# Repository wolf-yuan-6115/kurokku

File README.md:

# Kurokku

Kurokku is an ESP32 based Wi-Fi smart clock. Featuring E-ink display, it can pull weather data, calendar and display realtime clock. It is designed to be a simple and elegant clock that can be placed on a desk. There's also a SHT40 temperature and humidity sensor to provide more information.

Case was not designed and it's intended to just directly use screw as stand.

> [!NOTE]
> Please don't expect me to find a 3D model for e-ink display and include it.

> Note that display is not here yet because it's going to order seperately.

## Schematic

## Routing

## BOM

| Name | Qty | Total (USD) | Distributor |
| --- | --- | --- | --- |
| [Waveshare e-ink display](https://detail.tmall.com/item.htm?from=cart&id=763853854896&mi_id=0000evqKCP1iKHChQN8zlU8k7eiaN9Pw3tzSlfQsYnoQPNw&skuId=5256424296363&upStreamPrice=13068) | 1 | 19.50 | Taobao |
| [Seeed Xiao ESP32-S3](https://item.taobao.com/item.htm?from=cart&id=717378181472&mi_id=0000sOOkvg8oup2ws_yxejnEZ-Q6HdgFkvkQyJaaRKFnI_o&upStreamPrice=5500) | 1 | 8.20 | Taobao |
| PCB & PCBA | 1 | 28.96 | JLCPCB |
| Shipping | 1 | 0.5 | Taobao |
| Total | - | 57.16 | - |

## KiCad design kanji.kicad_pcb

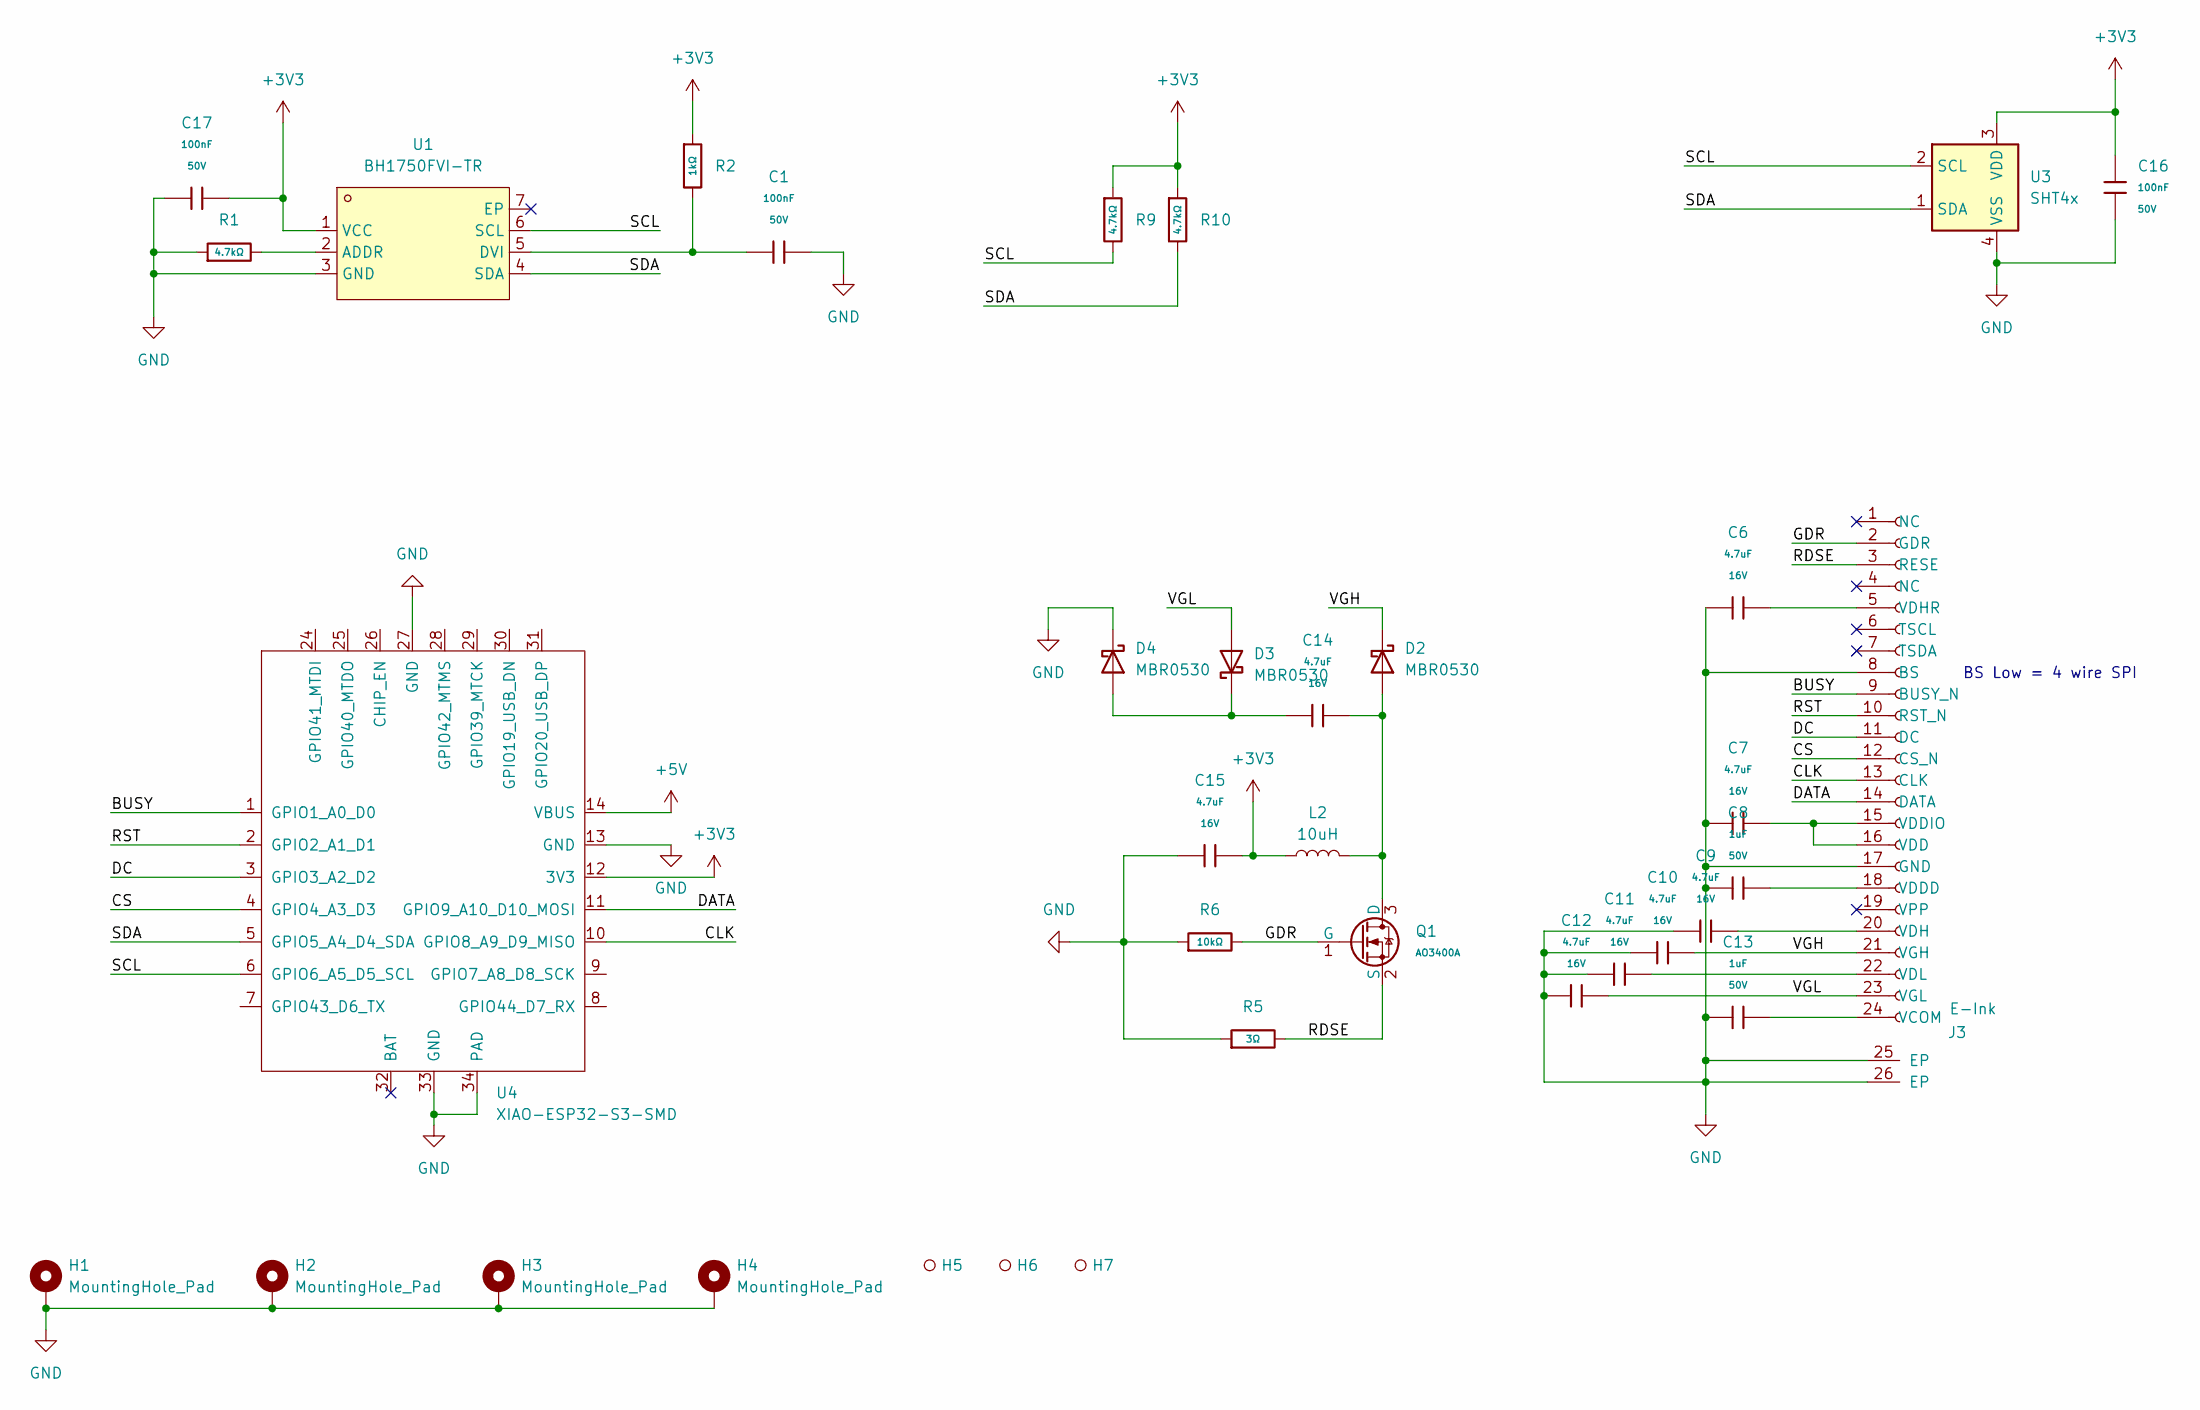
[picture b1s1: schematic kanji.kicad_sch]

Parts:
C1, C16, C17: 100nF; C_0603; Voltage Rated 50V; Tolerance ±10%; Part CC0603KRX7R9BB104; LCSC C14663
C6, C7, C9, C10, C11, C12, C14, C15: 4.7uF; C_0603; Voltage Rated 16V; Tolerance ±10%; Part CL10A475KO8NNNC; LCSC C19666
C8, C13: 1uF; C_0603; Voltage Rated 50V; Tolerance ±10%; Part CL10A105KB8NNNC; LCSC C15849
D2, D3, D4: MBR0530; D_SOD-123
H1, H2, H3, H4: MountingHole_Pad; MountingHole_3.2mm_M3_Pad_Via
H5, H6, H7: Hole_Tooling_JLCPCB
J3: E-Ink; FPC-SMD_AFC07-S24FCC-00
L2: 10uH; L_1008_2520Metric; LCSC C2049757
Q1: AO3400A; Q_SOT-23; Part AO3400A; LCSC C20917
R1, R9, R10: 4.7kΩ; R_0603; Overload Voltage (Max) 75V; Tolerance ±1%; Part 0603WAF4701T5E; LCSC C23162
R2: 1kΩ; R_0603; Overload Voltage (Max) 75V; Tolerance ±1%; Part 0603WAF1001T5E; LCSC C21190
R5: 3Ω; R_0603; Overload Voltage (Max) 75V; Tolerance ±1%; Part 0603WAF220KT5E; LCSC C23157
R6: 10kΩ; R_0603; Overload Voltage (Max) 75V; Tolerance ±1%; Part 0603WAF1002T5E; LCSC C25804
U1: BH1750FVI-TR; WSOF-6_L2.6-W1.6-P0.50-TL-EP; MPN BH1750FVI-TR; LCSC Part C78960
U3: SHT4x; Sensirion_DFN-4_1.5x1.5mm_P0.8mm_SHT4x_NoCentralPad; LCSC C2909890
U4: XIAO-ESP32-S3-SMD

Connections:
+3V3: C15.2, C16.1, C17.2, L2.1, R2.1, R9.1, R10.1, U1.1 (VCC), U3.3 (VDD), U4.12 (3V3)
+5V: U4.14 (VBUS)
/BUSY: J3.9 (BUSY_N), U4.1 (GPIO1_A0_D0)
/CLK: J3.13 (CLK), U4.10 (GPIO8_A9_D9_MISO)
/CS: J3.12 (CS_N), U4.4 (GPIO4_A3_D3)
/DATA: J3.14 (DATA), U4.11 (GPIO9_A10_D10_MOSI)
/DC: J3.11 (DC), U4.3 (GPIO3_A2_D2)
/GDR: J3.2 (GDR), Q1.1 (G), R6.2
/RDSE: J3.3 (RESE), Q1.2 (S), R5.2
/RST: J3.10 (RST_N), U4.2 (GPIO2_A1_D1)
/SCL: R9.2, U1.6 (SCL), U3.2 (SCL), U4.6 (GPIO6_A5_D5_SCL)
/SDA: R10.2, U1.4 (SDA), U3.1 (SDA), U4.5 (GPIO5_A4_D4_SDA)
/VGH: C10.2, D2.1 (K), J3.21 (VGH)
/VGL: C12.2, D3.2 (A), J3.23 (VGL)
GND: C1.2, C6.1, C7.1, C8.1, C9.1, C10.1, C11.1, C12.1, C13.1, C15.1, C16.2, C17.1, D4.1 (K), H1.1 (1_1), H2.1 (1_1), H3.1 (1_1), H4.1 (1_1), J3.8 (BS), J3.17 (GND), J3.25 (EP), J3.26 (EP), R1.1, R5.1, R6.1, U1.3 (GND), U3.4 (VSS), U4.13 (GND), U4.27 (GND), U4.33 (GND), U4.34 (PAD)
unnamed: C14.2, D2.2 (A), L2.2, Q1.3 (D)
unnamed: C14.1, D3.1 (K), D4.2 (A)
unnamed: C13.2, J3.24 (VCOM)
unnamed: C7.2, J3.15 (VDDIO), J3.16 (VDD)
unnamed: C8.2, J3.18 (VDDD)
unnamed: C9.2, J3.20 (VDH)
unnamed: C6.2, J3.5 (VDHR)
unnamed: C11.2, J3.22 (VDL)
unnamed: R1.2, U1.2 (ADDR)
unnamed: C1.1, R2.2, U1.5 (DVI)

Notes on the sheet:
BS Low = 4 wire SPI

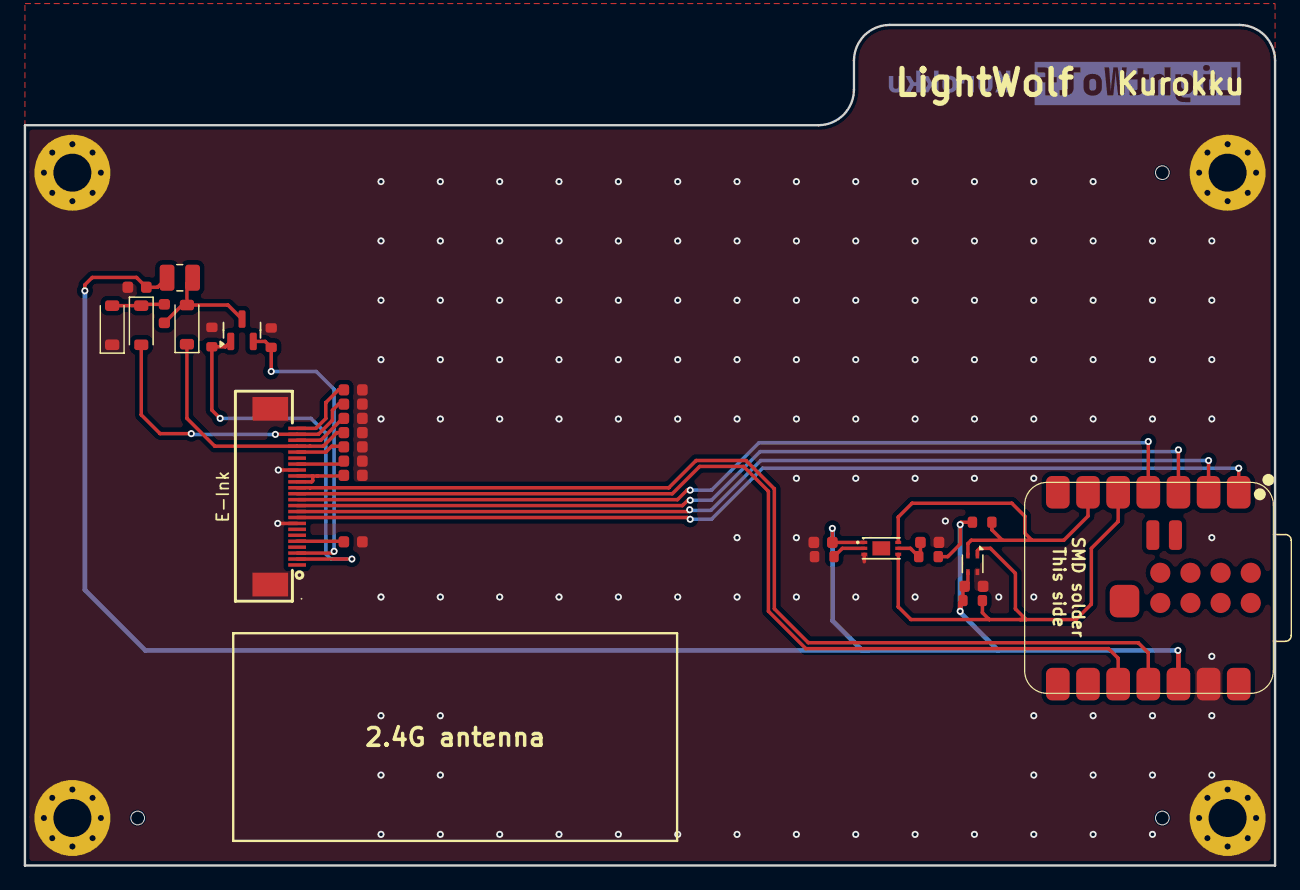
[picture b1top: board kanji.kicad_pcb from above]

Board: 2 copper layers, 105.3 x 70.8 mm, 35 parts (0 on the bottom side), 24 nets.

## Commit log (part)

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2026-06-23 feat: add case and update readme
